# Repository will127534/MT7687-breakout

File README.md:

# MT7687-breakout
A little breakout board for Acsip MT7687 module

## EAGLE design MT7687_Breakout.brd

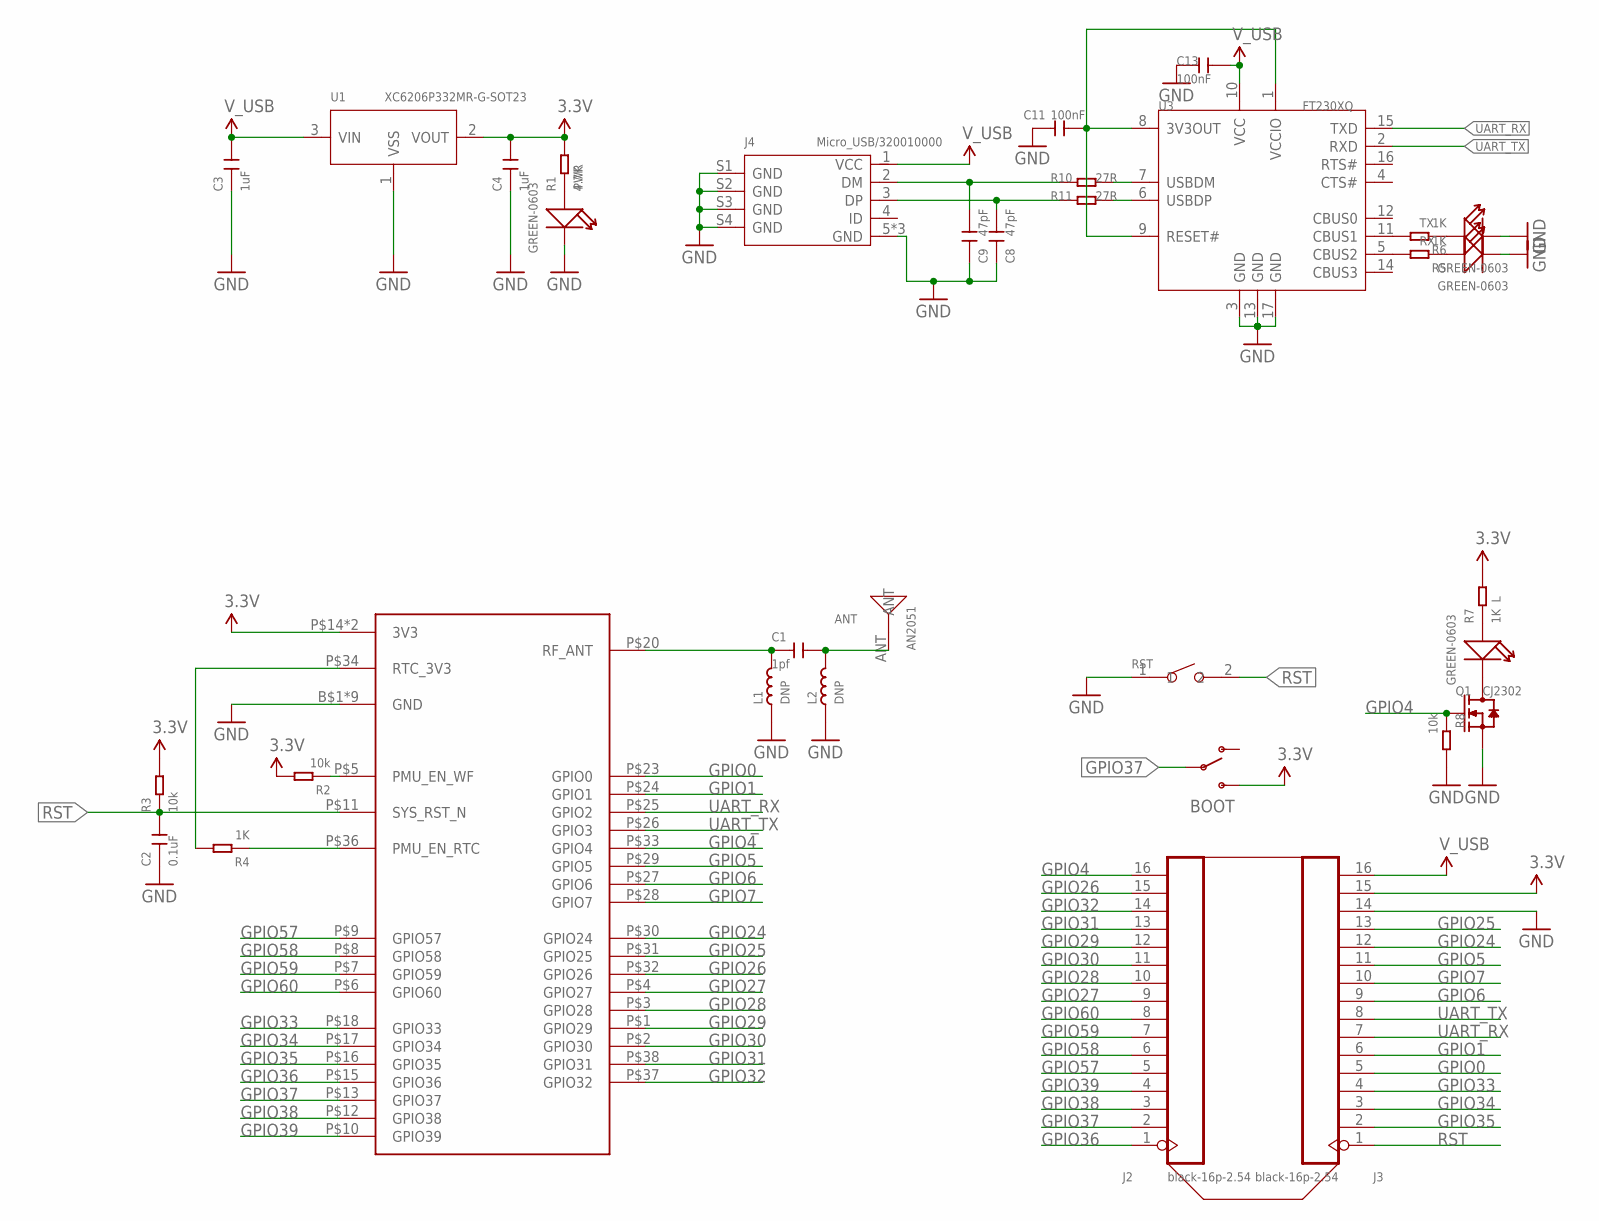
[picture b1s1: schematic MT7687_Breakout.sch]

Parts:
ANT: AN2051; ANT-SMD2P-5.05X2X1.07MM
BOOT: SWITCH-SPDTSMD; AYZ0202
C1: 1pf; C0402
C2: 0.1uF; C0402
C3, C4: 1uF; C0402
C8, C9: 47pF; C0402
C11, C13: 100nF; C0402
J2, J3: black-16p-2.54; H16-2.54
J4: Micro_USB/320010000; 5+4P-SMD-0.65-B
L: GREEN-0603; LED-0603
L1, L2: DNP; L0402
PWR: GREEN-0603; LED-0603
Q1: CJ2302; SOT-23
R1: 4.7K; R0402
R2, R3, R8: 10k; R0402
R4, R5, R6, R7: 1K; R0402
R10, R11: 27R; R0402
RST: SMD-BUTTON(2P-6.0X3.0X2.5MM)-DHT-1163S; SW2-4.0-6.0X3.0X2.5MM
RX: GREEN-0603; LED-0603
TX: GREEN-0603; LED-0603
U1: XC6206P332MR-G-SOT23; SOT-23
U3: FT230XQ; QFN-16
U$1: MT7687

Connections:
3.3V: BOOT.3 (S), C4.2, J3.15, R1.2, R2.2, R3.2, R7.2, U1.2 (VOUT), U$1.P$14 (3V3), U$1.P$39 (3V3)
GND: C2.1, C3.1, C4.1, C8.1, C9.1, C11.1, C13.1, J3.14, J4.5 (GND), J4.S1 (GND), J4.S2 (GND), J4.S3 (GND), J4.S4 (GND), J4.S5 (GND), J4.S6 (GND), L1.1, L2.1, PWR.-, Q1.2 (S), R8.2, RST.1, RX.-, TX.-, U1.1 (VSS), U3.3 (GND), U3.13 (GND), U3.17 (GND), U$1.B$1 (GND), U$1.B$2 (GND), U$1.B$3 (GND), U$1.B$4 (GND), U$1.P$19 (GND), U$1.P$21 (GND), U$1.P$22 (GND), U$1.P$35 (GND), U$1.P$40 (GND)
GPIO0: J3.5, U$1.P$23 (GPIO0)
GPIO1: J3.6, U$1.P$24 (GPIO1)
GPIO4: J2.16, Q1.1 (G), R8.1, U$1.P$33 (GPIO4)
GPIO5: J3.11, U$1.P$29 (GPIO5)
GPIO6: J3.9, U$1.P$27 (GPIO6)
GPIO7: J3.10, U$1.P$28 (GPIO7)
GPIO24: J3.12, U$1.P$30 (GPIO24)
GPIO25: J3.13, U$1.P$31 (GPIO25)
GPIO26: J2.15, U$1.P$32 (GPIO26)
GPIO27: J2.9, U$1.P$4 (GPIO27)
GPIO28: J2.10, U$1.P$3 (GPIO28)
GPIO29: J2.12, U$1.P$1 (GPIO29)
GPIO30: J2.11, U$1.P$2 (GPIO30)
GPIO31: J2.13, U$1.P$38 (GPIO31)
GPIO32: J2.14, U$1.P$37 (GPIO32)
GPIO33: J3.4, U$1.P$18 (GPIO33)
GPIO34: J3.3, U$1.P$17 (GPIO34)
GPIO35: J3.2, U$1.P$16 (GPIO35)
GPIO36: J2.1, U$1.P$15 (GPIO36)
GPIO37: BOOT.2, J2.2, U$1.P$13 (GPIO37)
GPIO38: J2.3, U$1.P$12 (GPIO38)
GPIO39: J2.4, U$1.P$10 (GPIO39)
GPIO57: J2.5, U$1.P$9 (GPIO57)
GPIO58: J2.6, U$1.P$8 (GPIO58)
GPIO59: J2.7, U$1.P$7 (GPIO59)
GPIO60: J2.8, U$1.P$6 (GPIO60)
unnamed: R2.1, U$1.P$5 (PMU_EN_WF)
unnamed: C1.1, L1.2, U$1.P$20 (RF_ANT)
unnamed: ANT.ANT, C1.2, L2.2
unnamed: PWR.+, R1.1
unnamed: R4.1, U$1.P$36 (PMU_EN_RTC)
unnamed: L.+, R7.1
unnamed: C11.2, U3.1 (VCCIO), U3.8 (3V3OUT), U3.9 (RESET#)
unnamed: L.-, Q1.3 (D)
unnamed: R4.2, U$1.P$34 (RTC_3V3)
unnamed: R10.2, U3.7 (USBDM)
unnamed: R11.2, U3.6 (USBDP)
unnamed: C9.2, J4.2 (DM), R10.1
unnamed: C8.2, J4.3 (DP), R11.1
unnamed: R5.1, RX.+
unnamed: R6.1, TX.+
unnamed: R5.2, U3.5 (CBUS2)
unnamed: R6.2, U3.11 (CBUS1)
RST: C2.2, J3.1, R3.1, RST.2, U$1.P$11 (SYS_RST_N)
UART_RX: J3.7, U3.15 (TXD), U$1.P$25 (GPIO2)
UART_TX: J3.8, U3.2 (RXD), U$1.P$26 (GPIO3)
V_USB: C3.2, C13.2, J3.16, J4.1 (VCC), U1.3 (VIN), U3.10 (VCC)

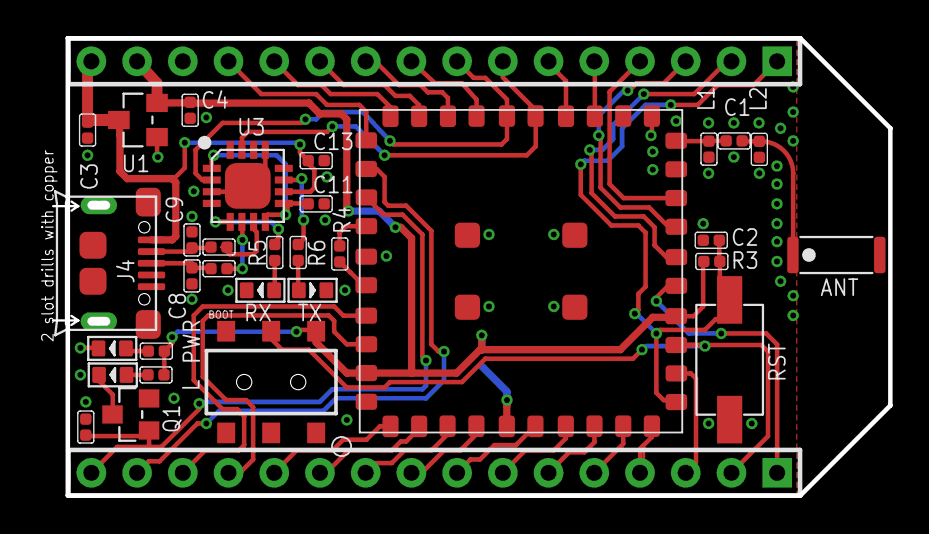
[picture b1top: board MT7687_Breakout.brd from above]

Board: 2 copper layers, 47.1 x 25.1 mm, 34 parts (1 on the bottom side), 49 nets.

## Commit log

2016-08-12 init

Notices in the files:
parts and their libraries:
SparkFun-Electromechanical: Licensing: Creative Commons ShareAlike 4.0 International - https://creativecommons.org/licenses/by-sa/4.0
